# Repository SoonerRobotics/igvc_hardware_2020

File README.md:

# igvc_hardware_2020

PCBs for the IGVC competition.

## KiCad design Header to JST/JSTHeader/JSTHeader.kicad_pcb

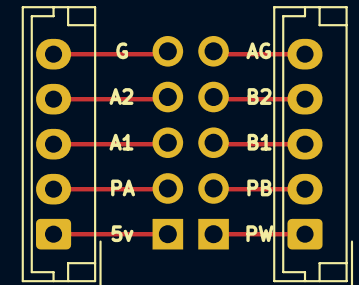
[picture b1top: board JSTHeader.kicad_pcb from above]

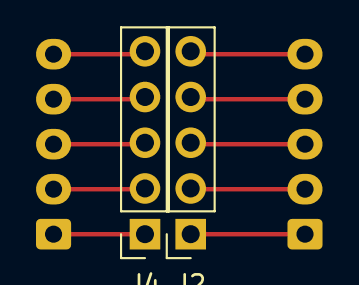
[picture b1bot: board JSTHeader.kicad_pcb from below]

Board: 2 copper layers, 4 parts (2 on the bottom side), 10 nets.

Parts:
J1, J3: Conn_01x05_Male; JST_EH_B5B-EH-A_1x05_P2.50mm_Vertical
J2, J4: Conn_01x05_Female; PinSocket_1x05_P2.54mm_Vertical

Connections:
unnamed: J1.1, J2.1
unnamed: J1.2, J2.2
unnamed: J1.3, J2.3
unnamed: J1.4, J2.4
unnamed: J1.5, J2.5
unnamed: J3.1, J4.1
unnamed: J3.2, J4.2
unnamed: J3.3, J4.3
unnamed: J3.4, J4.4
unnamed: J3.5, J4.5

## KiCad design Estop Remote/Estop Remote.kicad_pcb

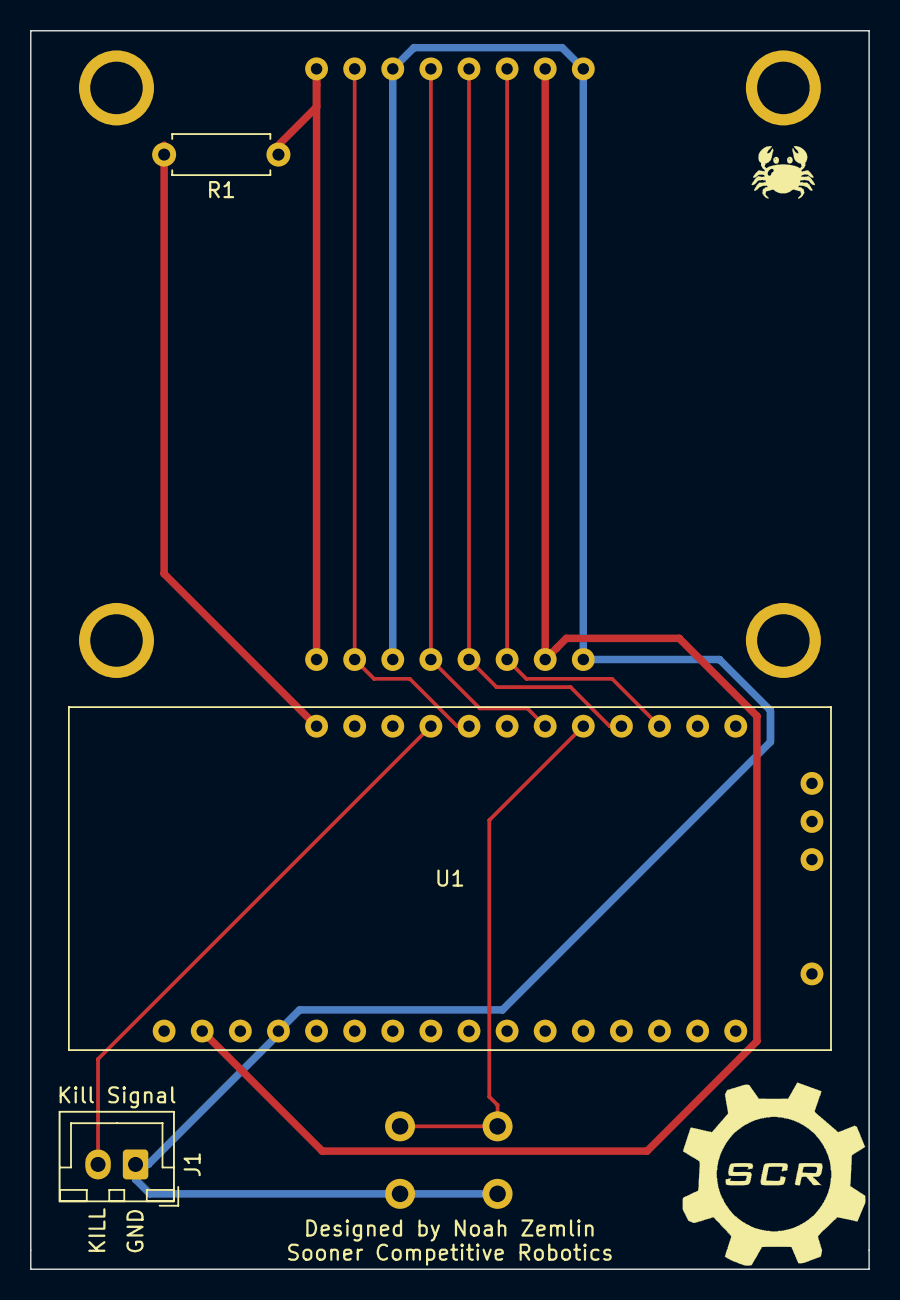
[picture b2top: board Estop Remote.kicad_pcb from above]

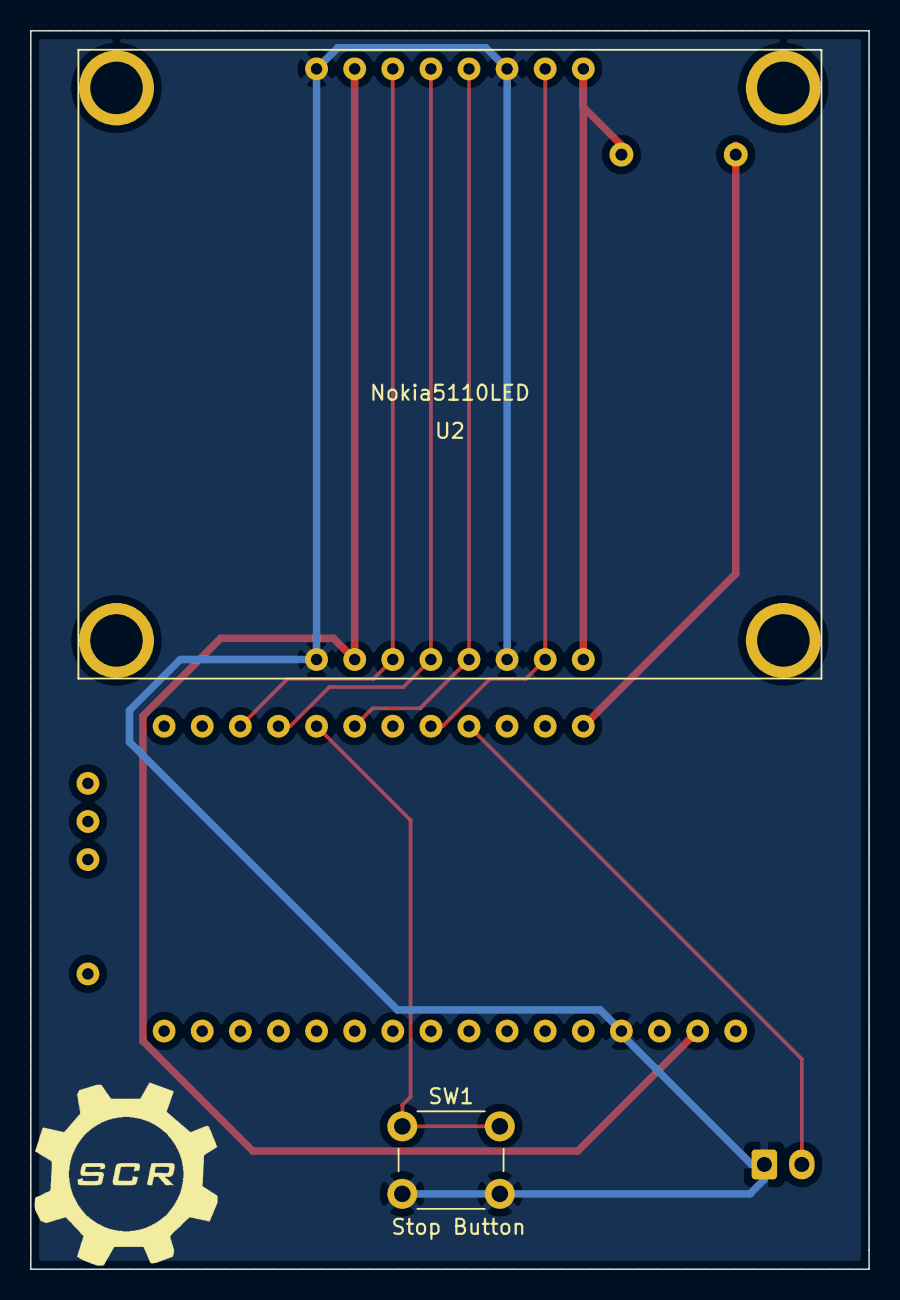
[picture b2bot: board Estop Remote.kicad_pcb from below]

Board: 2 copper layers, 55.9 x 82.6 mm, 5 parts (2 on the bottom side), 10 nets.

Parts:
J1: Kill Signal; JST_XH_B2B-XH-A_1x02_P2.50mm_Vertical
R1: 560; R_Axial_DIN0207_L6.3mm_D2.5mm_P7.62mm_Horizontal
SW1: Stop Button; SW_PUSH_6mm_H5mm
U1: AdafruitFeatherM0LoRa
U2: Nokia5110LED; AdafruitNokia5110

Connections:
+3V3: U1.31, U2.2
+5V: R1.2, U1.16
DSPL_DC: U1.10, U2.5
DSPL_DIN: U1.8, U2.4
DSPL_RST: U1.12, U2.7
DSPL_SCLK: U1.7, U2.3
GND: J1.1, SW1.2, U1.29, U2.1, U2.6
unnamed: R1.1, U2.8
SIG_KILL: J1.2, U1.13
SIG_STOP: SW1.1, U1.9

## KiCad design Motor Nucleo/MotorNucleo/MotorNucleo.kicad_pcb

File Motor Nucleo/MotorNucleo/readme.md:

# Nucleo motor controller board

The speed of the motor controller is controlled using PWM and the direction of the motor is controlled using the enable pins A and B. 

Each side of the robot has two motors connected together to provide more torque. The motors share a PWM signal and enable pins on their respective sides.

Vin is supplied using a buck converter that converts 12V to 5V

## Components
1x [Nucleo-L432](https://www.st.com/resource/en/datasheet/stm32l432kc.pdf)

4x 4 port JST connector

2x 3 port JST connector

1x 2 port JST connector
## Block diagram

###TODO

## Designers

- Tyler Julian - Designer - [TylerJulian](https://github.com/tylerjulian)

## Built With

- KiCAD - Used to create schematics and pcbs. 

## Errata
* revision 1 A level shifter was not needed due to the GP I/O pins being 5 volt tolerant. The schematic was also needlessly complicated and hard to read.

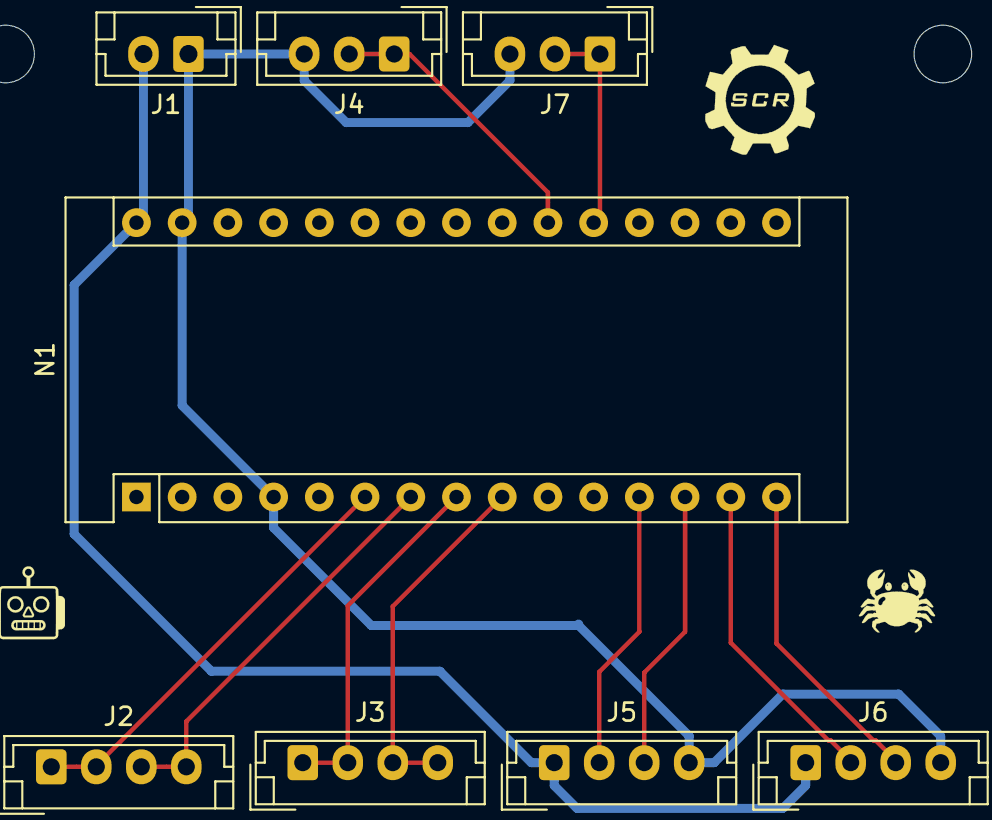
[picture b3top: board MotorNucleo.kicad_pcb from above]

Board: 2 copper layers, 8 parts (0 on the bottom side), 12 nets.

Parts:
J1: JST_01x02; JST_EH_B2B-EH-A_1x02_P2.50mm_Vertical
J2, J3, J5, J6: JST_01x04; JST_EH_B4B-EH-A_1x04_P2.50mm_Vertical
J4, J7: JST_01x03; JST_EH_B3B-EH-A_1x03_P2.50mm_Vertical
N1: Nucleo-L432KC; Arduino_Nano

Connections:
+5V: J1.2, J5.1, J6.1, N1.30
ENCODER_LEFT_A: J5.2, N1.12
ENCODER_LEFT_B: J5.3, N1.13
ENCODER_RIGHT_A: J6.2, N1.14
ENCODER_RIGHT_B: J6.3, N1.15
GND: J1.1, J4.3, J5.4, J6.4, J7.3, N1.4, N1.29
LEFT_EN_A: J2.1, J2.2, N1.6
LEFT_EN_B: J2.3, J2.4, N1.7
LEFT_PWM: J7.1, J7.2, N1.20
RIGHT_EN_A: J3.1, J3.2, N1.8
RIGHT_EN_B: J3.3, J3.4, N1.9
RIGHT_PWM: J4.1, J4.2, N1.21

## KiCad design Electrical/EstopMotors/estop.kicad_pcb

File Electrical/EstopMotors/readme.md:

# Motor controller estop overide

The direction of the motor is controlled with using two pins. Enable will override the inputs and output low when enable is low. 

The schematic has enough outputs for two motors.

## Components
4x [irf9530n mosfets](http://www.vishay.com/docs/91076/sihf9530.pdf)

8x 10k resistors

4x 1k resistors

2x 4 port JST connector

1x 3 port JST connector
## Block diagram

## Designers

- Tyler Julian - Designer - [TylerJulian](https://github.com/tylerjulian)

## Built With

- KiCAD - Used to create schematics and pcbs. 

## Errata
* revision 1's PCBs had the incorrect footprint for the jst connectors and the drain and source of the mosfets were switched.
* revision 2 had the wrong mosfet type. Intended mosfet is p-channel instead of n-channel. Updated schematic to reflect the switch to p-channel.

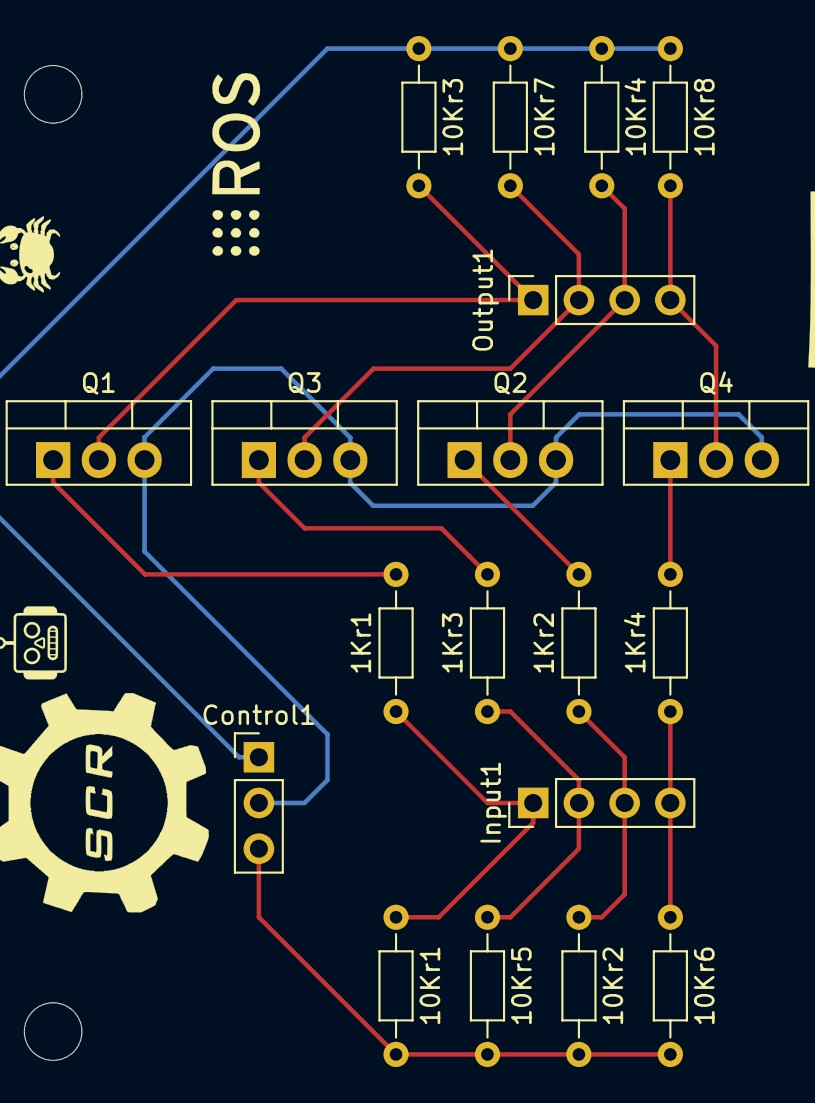
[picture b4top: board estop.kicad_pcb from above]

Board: 2 copper layers, 23 parts (0 on the bottom side), 15 nets.

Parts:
1Kr1, 1Kr2, 1Kr3, 1Kr4, 10Kr1, 10Kr2, 10Kr3, 10Kr4, 10Kr5, 10Kr6, 10Kr7, 10Kr8: ROX5SSJ1K8; R_Axial_DIN0204_L3.6mm_D1.6mm_P7.62mm_Horizontal
Control1: Conn_01x03; PinHeader_1x03_P2.54mm_Vertical
Input1: Conn_01x04; PinHeader_1x04_P2.54mm_Vertical
MountingHole1, MountingHole2, MountingHole3, MountingHole4: MOUNTINGHOLE; MountingHole_3.2mm_M3
Output1: Conn_01x04; PinSocket_1x04_P2.54mm_Vertical
Q1, Q2, Q3, Q4: IRF9530N; TO-220-3_Vertical

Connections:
Enable: Control1.2, Q1.3, Q2.3, Q3.3, Q4.3
GND: 10Kr3.1, 10Kr4.1, 10Kr7.1, 10Kr8.1, Control1.1
Input1: 1Kr1.1, 10Kr1.1, Input1.1
Input2: 1Kr3.1, 10Kr5.1, Input1.2
Input3: 1Kr2.1, 10Kr2.1, Input1.3
Input4: 1Kr4.1, 10Kr6.1, Input1.4
unnamed: 1Kr1.2, Q1.1
unnamed: 1Kr2.2, Q2.1
unnamed: 1Kr3.2, Q3.1
unnamed: 1Kr4.2, Q4.1
Output1: 10Kr3.2, Output1.1, Q1.2
Output2: 10Kr7.2, Output1.2, Q3.2
Output3: 10Kr4.2, Output1.3, Q2.2
Output4: 10Kr8.2, Output1.4, Q4.2
VCC: 10Kr1.2, 10Kr2.2, 10Kr5.2, 10Kr6.2, Control1.3

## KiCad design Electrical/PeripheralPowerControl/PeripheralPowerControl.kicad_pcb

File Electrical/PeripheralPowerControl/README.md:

# Peripheral Power Control Board

Enable and disable power to a peripheral component (such as a camera, raspberry pi, or arduino) and regulate voltage for the peripheral.

## Components
- [LM2956 Breakout Board](https://www.amazon.com/LM2596-Converter-3-0-40V-1-5-35V-Supply/dp/B01GJ0SC2C) - Buck Converter (can find on Amazon easily)
- [IPP120P04P4L03AKSA1](https://www.mouser.co.il/ProductDetail/Infineon-Technologies/IPP120P04P4L03AKSA1?qs=sGAEpiMZZMshyDBzk1%2FWi4lI00SCTc047yeVAvMQSdk%3D) - 120A rated Power PMOS
- [64600001003](https://www.mouser.co.il/ProductDetail/Littelfuse/64600001003?qs=J2dJc02fMkr9fpR3CPjt3Q==) - Fuse Holder

## Images
insert top view picture of PCB

## Designers

- Justin Kleiber - Designer - [jkleiber](https://github.com/jkleiber)

## Built With

- KiCAD - The PCB design software used

## Errata

TBD

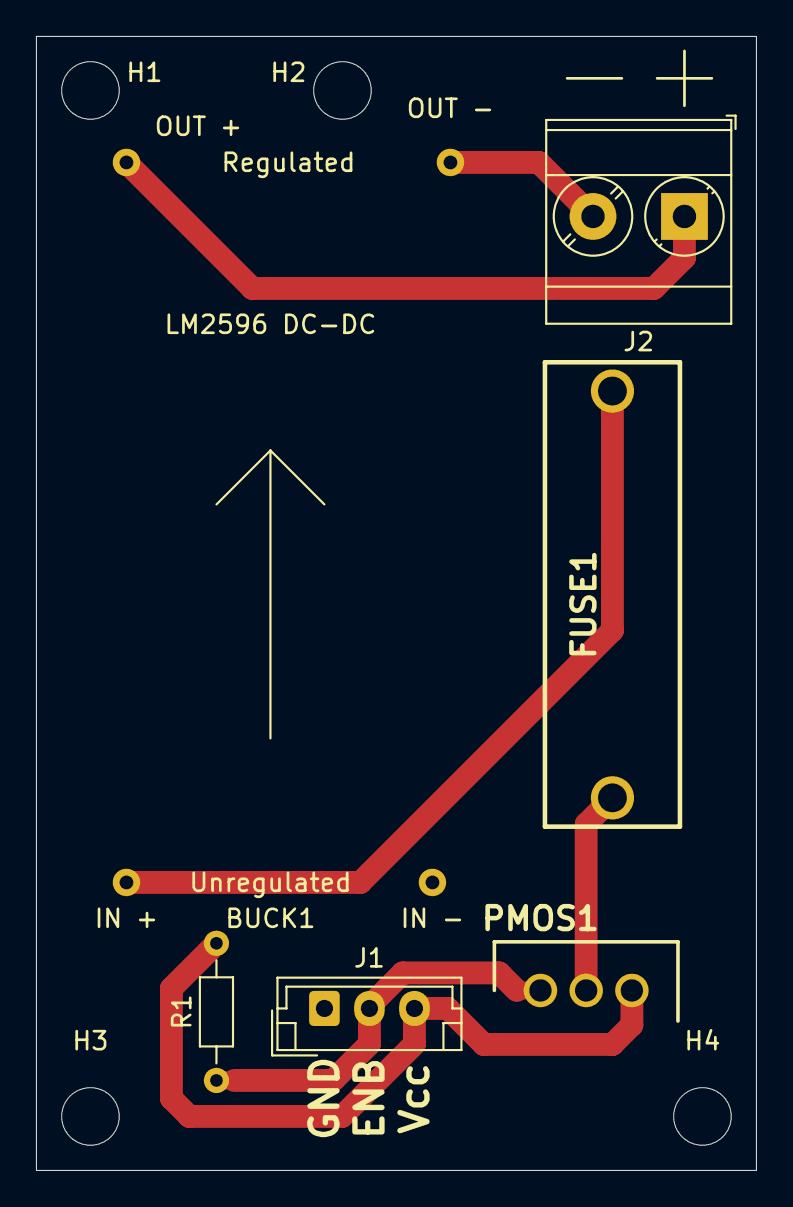
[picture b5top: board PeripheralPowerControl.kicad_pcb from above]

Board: 2 copper layers, 40.0 x 63.0 mm, 10 parts (0 on the bottom side), 7 nets.

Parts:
BUCK1: LM2596
FUSE1: 64600001003; 646-SERIESHOLDER
H1, H2, H3, H4: MountingHole; MountingHole_3.2mm_M3
J1: Conn_01x03; JST_EH_B3B-EH-A_1x03_P2.50mm_Vertical
J2: Screw_Terminal_01x02; TerminalBlock_Phoenix_MKDS-3-2-5.08_1x02_P5.08mm_Horizontal
PMOS1: IPP120P04P4L03AKSA1; TO254P440X1000X2110-3P
R1: R; R_Axial_DIN0204_L3.6mm_D1.6mm_P7.62mm_Horizontal

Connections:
GND: BUCK1.1, J1.1
unnamed: BUCK1.2, FUSE1.2
unnamed: BUCK1.3, J2.2
unnamed: BUCK1.4, J2.1
unnamed: FUSE1.1, PMOS1.2
unnamed: J1.2, PMOS1.1, R1.1
unnamed: J1.3, PMOS1.3, R1.2

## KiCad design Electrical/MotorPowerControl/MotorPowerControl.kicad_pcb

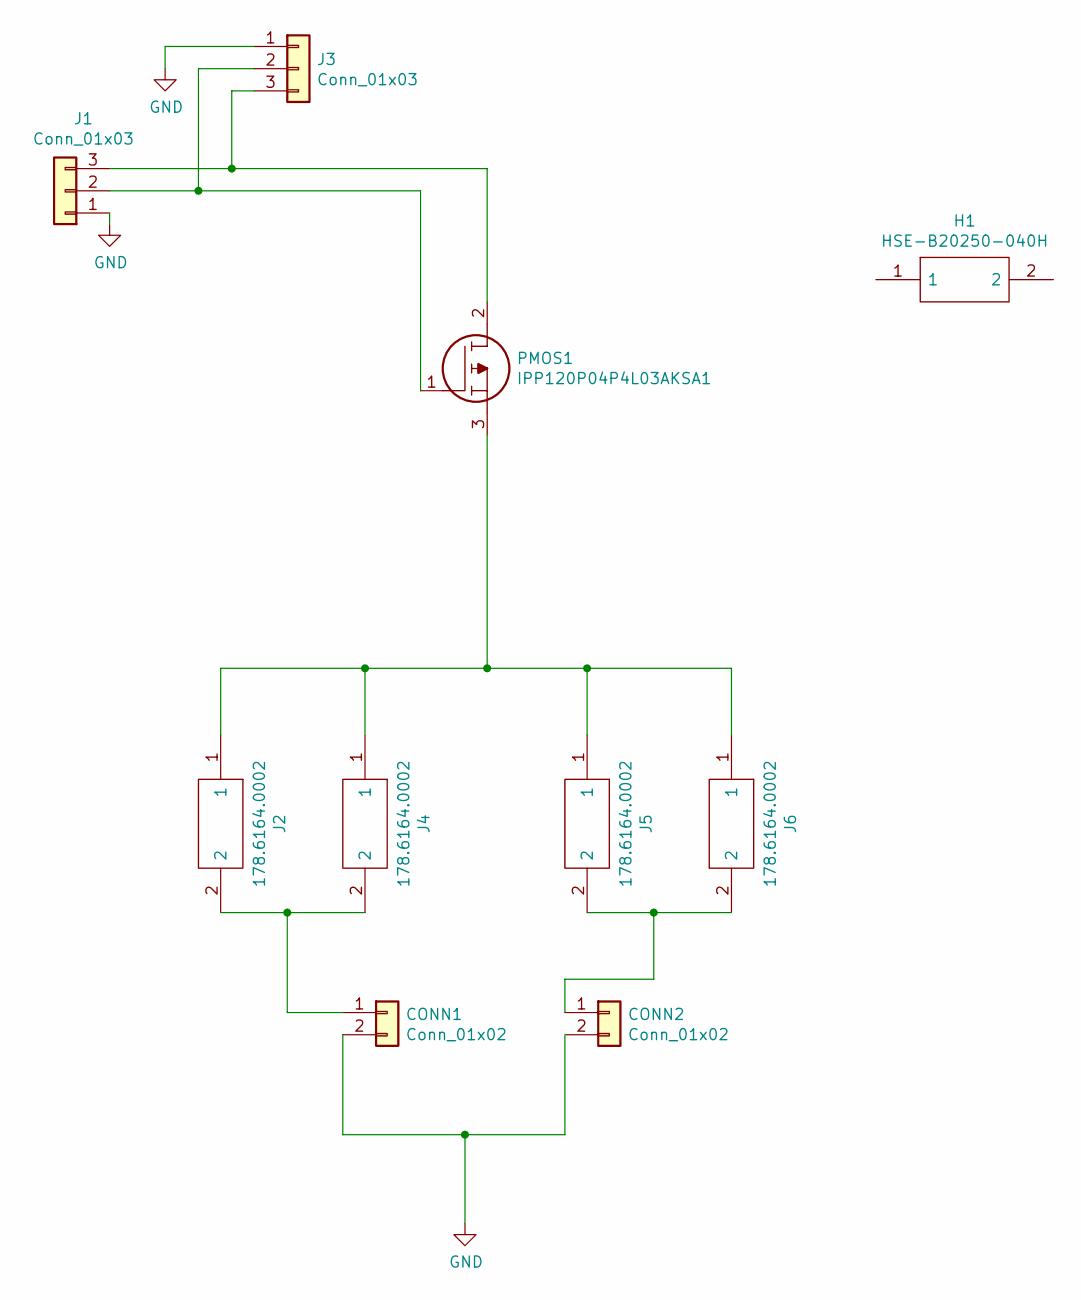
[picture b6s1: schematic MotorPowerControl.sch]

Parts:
CONN1, CONN2: Conn_01x02; SolderWirePad_1x02_P7.62mm_Drill2.5mm
H1: HSE-B20250-040H; HSEB20250040H; Mouser Part Number 490-HSE-B20250-040H
J1, J3: Conn_01x03; SolderWirePad_1x03_P7.62mm_Drill2.5mm
J2, J4, J5, J6: 178.6164.0002; 178.6164.0002_1; Mouser Part Number 576-178.6164.0002
PMOS1: IPP120P04P4L03AKSA1; TO254P440X1000X2110-3P; Mouser Part Number 726-IPP120P04P4L03AK

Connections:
GND: CONN1.2, CONN2.2, J1.1, J3.1
unnamed: CONN1.1, J2.2, J4.2
unnamed: CONN2.1, J5.2, J6.2
unnamed: J1.2, J3.2, PMOS1.1
unnamed: J1.3, J3.3, PMOS1.2
unnamed: J2.1, J4.1, J5.1, J6.1, PMOS1.3

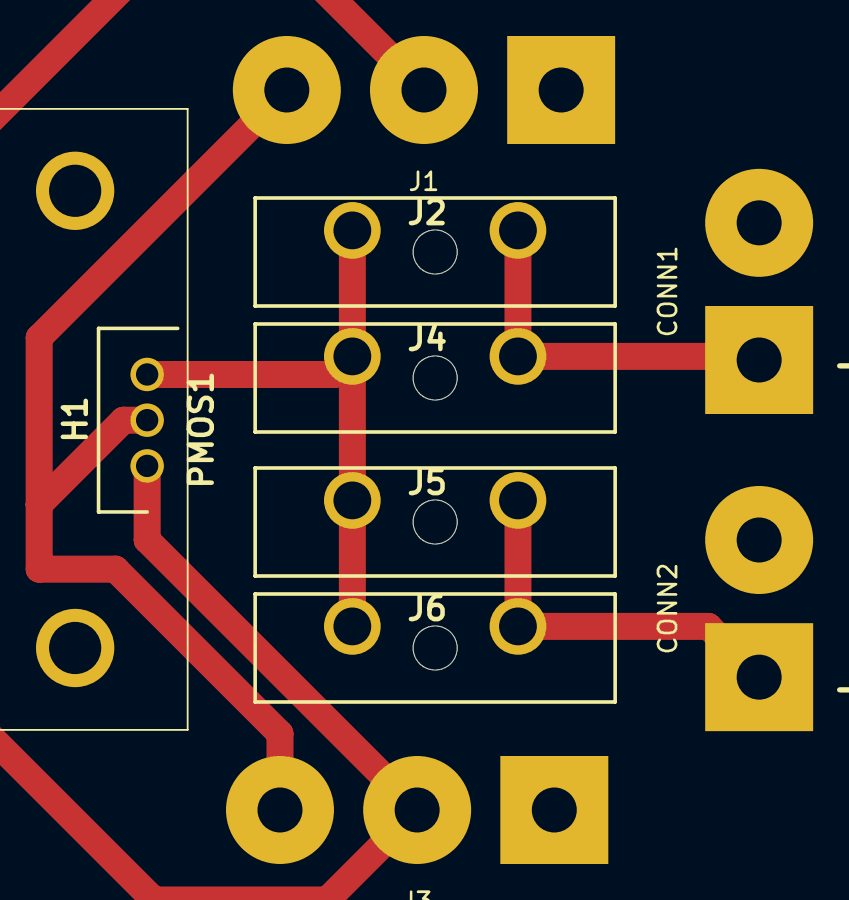
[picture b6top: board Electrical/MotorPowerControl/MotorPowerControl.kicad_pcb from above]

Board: 2 copper layers, 10 parts (0 on the bottom side), 6 nets.

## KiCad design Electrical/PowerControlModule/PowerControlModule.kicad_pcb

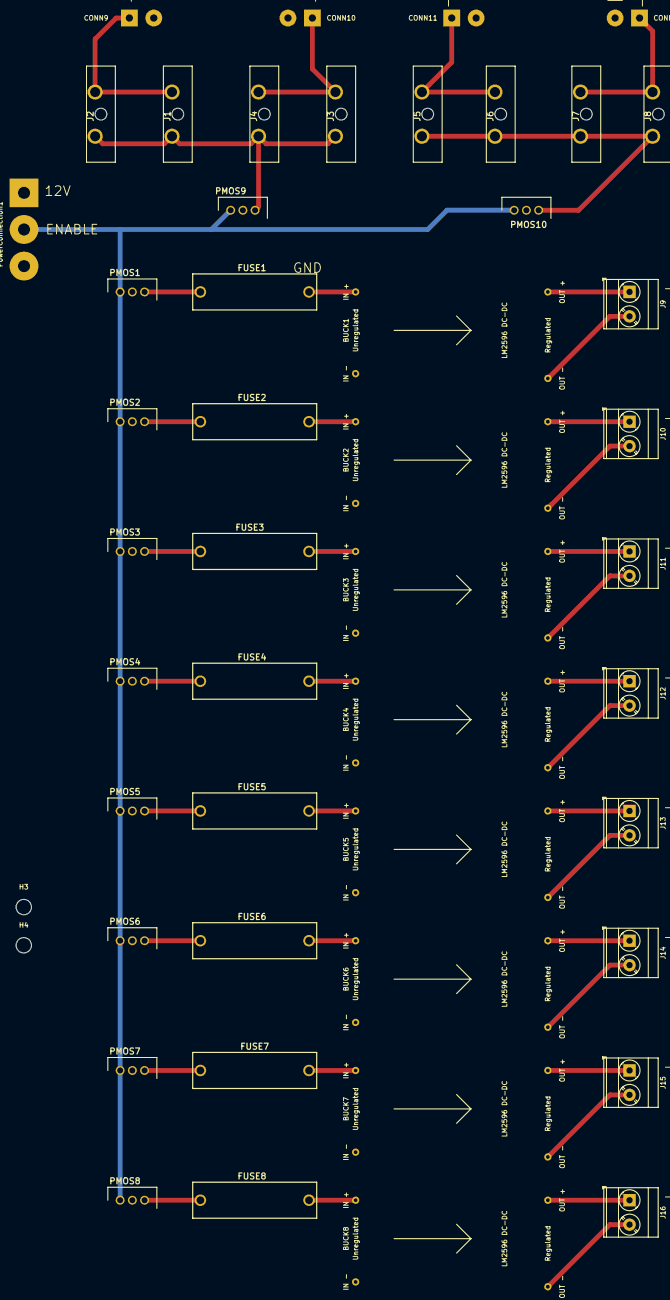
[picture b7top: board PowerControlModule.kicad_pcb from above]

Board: 4 copper layers, 51 parts (0 on the bottom side), 41 nets.

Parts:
BUCK1, BUCK2, BUCK3, BUCK4, BUCK5, BUCK6, BUCK7, BUCK8: LM2596
CONN9, CONN10, CONN11, CONN12: Conn_01x02; SolderWirePad_1x02_P5.08mm_Drill1.5mm
FUSE1, FUSE2, FUSE3, FUSE4, FUSE5, FUSE6, FUSE7, FUSE8: 64600001003; 646-SERIESHOLDER
H1, H2, H3, H4: MountingHole; MountingHole_3.2mm_M3
J1, J2, J3, J4, J5, J6, J7, J8: 178.6164.0002; 178.6164.0002_1
J9, J10, J11, J12, J13, J14, J15, J16: Screw_Terminal_01x02; TerminalBlock_Phoenix_MKDS-3-2-5.08_1x02_P5.08mm_Horizontal
PMOS1, PMOS2, PMOS3, PMOS4, PMOS5, PMOS6, PMOS7, PMOS8, PMOS9, PMOS10: IPP120P04P4L03AKSA1; TO254P440X1000X2110-3P
PowerConnection1: Conn_01x03; SolderWirePad_1x03_P7.62mm_Drill2.5mm

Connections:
+12V: PMOS1.2, PMOS2.2, PMOS3.2, PMOS4.2, PMOS5.2, PMOS6.2, PMOS7.2, PMOS8.2, PMOS9.2, PMOS10.2, PowerConnection1.1
/ENABLE: PMOS1.1, PMOS2.1, PMOS3.1, PMOS4.1, PMOS5.1, PMOS6.1, PMOS7.1, PMOS8.1, PMOS9.1, PMOS10.1, PowerConnection1.2
GND: BUCK1.1, BUCK2.1, BUCK3.1, BUCK4.1, BUCK5.1, BUCK6.1, BUCK7.1, BUCK8.1, CONN9.2, CONN10.2, CONN11.2, CONN12.2, PowerConnection1.3
unnamed: BUCK1.2, FUSE1.2
unnamed: BUCK1.3, J9.2
unnamed: BUCK1.4, J9.1
unnamed: BUCK2.2, FUSE2.2
unnamed: BUCK2.3, J10.2
unnamed: BUCK2.4, J10.1
unnamed: BUCK3.2, FUSE3.2
unnamed: BUCK3.3, J11.2
unnamed: BUCK3.4, J11.1
unnamed: BUCK4.2, FUSE4.2
unnamed: BUCK4.3, J12.2
unnamed: BUCK4.4, J12.1
unnamed: BUCK5.2, FUSE5.2
unnamed: BUCK5.3, J13.2
unnamed: BUCK5.4, J13.1
unnamed: BUCK6.2, FUSE6.2
unnamed: BUCK6.3, J14.2
unnamed: BUCK6.4, J14.1
unnamed: BUCK7.2, FUSE7.2
unnamed: BUCK7.3, J15.2
unnamed: BUCK7.4, J15.1
unnamed: BUCK8.2, FUSE8.2
unnamed: BUCK8.3, J16.2
unnamed: BUCK8.4, J16.1
unnamed: CONN9.1, J1.2, J2.2
unnamed: CONN10.1, J3.2, J4.2
unnamed: CONN11.1, J5.2, J6.2
unnamed: CONN12.1, J7.2, J8.2
unnamed: FUSE1.1, PMOS1.3
unnamed: FUSE2.1, PMOS2.3
unnamed: FUSE3.1, PMOS3.3
unnamed: FUSE4.1, PMOS4.3
unnamed: FUSE5.1, PMOS5.3
unnamed: FUSE6.1, PMOS6.3
unnamed: FUSE7.1, PMOS7.3
unnamed: FUSE8.1, PMOS8.3
unnamed: J1.1, J2.1, J3.1, J4.1, PMOS9.3
unnamed: J5.1, J6.1, J7.1, J8.1, PMOS10.3

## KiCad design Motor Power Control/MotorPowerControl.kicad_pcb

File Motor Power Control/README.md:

# Motor Power Control Board

Enable and disable power to a peripheral component (such as a camera, Raspberry Pi, or Arduino) and regulate voltage for the peripheral.

## Components

- [LM2956 Breakout Board](https://www.amazon.com/LM2596-Converter-3-0-40V-1-5-35V-Supply/dp/B01GJ0SC2C) - Buck Converter (can find on Amazon easily)
- [IPP120P04P4L03AKSA1](https://www.mouser.co.il/ProductDetail/Infineon-Technologies/IPP120P04P4L03AKSA1?qs=sGAEpiMZZMshyDBzk1%2FWi4lI00SCTc047yeVAvMQSdk%3D) - 120A rated Power PMOS
- [64600001003](https://www.mouser.co.il/ProductDetail/Littelfuse/64600001003?qs=J2dJc02fMkr9fpR3CPjt3Q==) - Fuse Holder

## Images

- insert top view picture of PCB

## Designers

- XXX - YYY - [ZZZ](https://github.com/jkleiber)

## Built With

- KiCAD - The PCB design software used

## Errata

- TBD

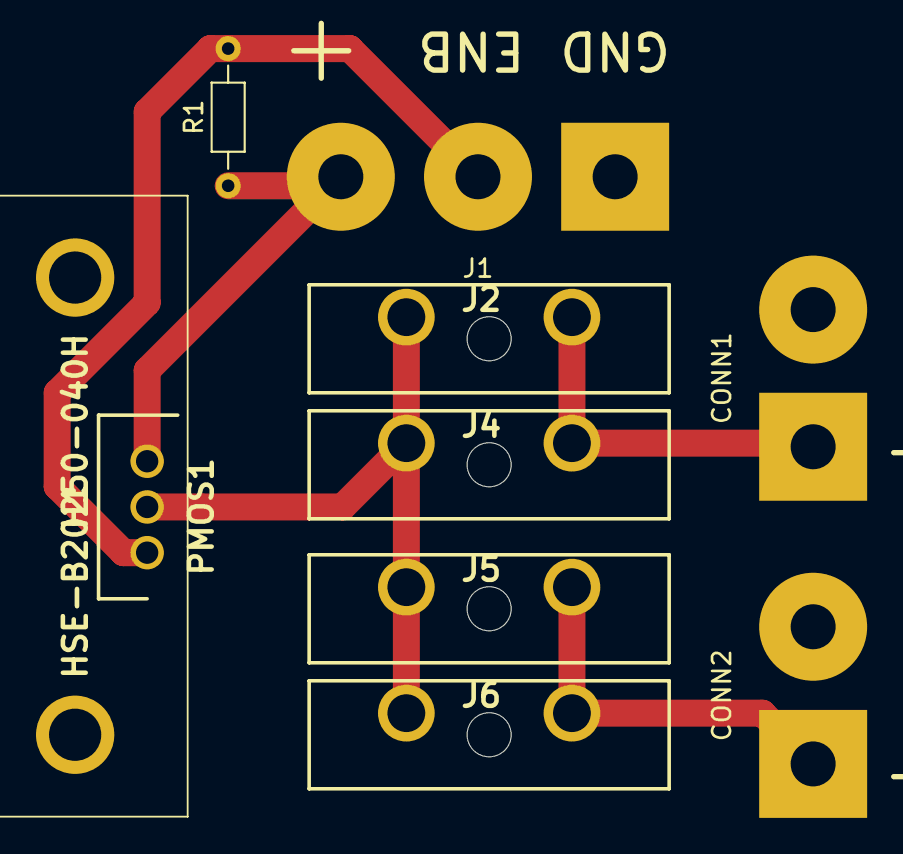
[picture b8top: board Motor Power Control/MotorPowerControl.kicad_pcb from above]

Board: 2 copper layers, 14 parts (0 on the bottom side), 6 nets.

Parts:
CONN1, CONN2: Conn_01x02; SolderWirePad_1x02_P7.62mm_Drill2.5mm
H1: HSE-B20250-040H; HSEB20250040H
H2, H3, H4, H5: MountingHole; MountingHole_3.2mm_M3
J1: Conn_01x03; SolderWirePad_1x03_P7.62mm_Drill2.5mm
J2, J4, J5, J6: 178.6164.0002; 178.6164.0002_1
PMOS1: IPP120P04P4L03AKSA1; TO254P440X1000X2110-3P
R1: R; R_Axial_DIN0204_L3.6mm_D1.6mm_P7.62mm_Horizontal

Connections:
GND: CONN1.2, CONN2.2, J1.1
unnamed: CONN1.1, J2.2, J4.2
unnamed: CONN2.1, J5.2, J6.2
unnamed: J1.2, PMOS1.1, R1.2
unnamed: J1.3, PMOS1.3, R1.1
unnamed: J2.1, J4.1, J5.1, J6.1, PMOS1.2

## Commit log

2019-08-02 Initial schematic for the transmitter/receiver estop. Does not include power sources in schematic.
2019-09-12 Begins work on the power control module
2019-09-12 Testing import of power mosfet
2019-09-20 posted picture of motor control circuit
2019-09-20 Lays out peripherals and motor control power distribution
    Paginates the schematic for ease of editing
2019-09-24 Adds new part library for SCR stuff. Gets buck converters and connectors to show up on PCB layout
2019-09-24 Lays out power distribution board on PCB. Need to make 4 layer setup before routing. Also need to change motor output footprint
2019-09-25 Routes PCM as a 4 layer board
2019-09-25 Fixes silkscreen stuff and adds ground connection for motor control battery connection
2019-09-25 Power control module grounding and power plane fixes
2019-09-26 Rearranges mosfets, fuses and buck converters in correct order. Need to add heatsinks to design and confirm hole sizes. Also need to add safety module eventually
2019-09-26 Peripheral changes and rewired PCB
2019-10-02 Splits project into multiple modules, peripherals, motors, and safety
2019-10-02 Adds ground plane to the peripheral board
2019-10-03 Updates BOM for motor power control
2019-10-08 Verified Peripheral and Motor power controllers
2019-10-22 Adafruit M0 LoRa Control
2019-11-26 Upload motor estop schematic and pcb
2020-01-29 Adds notes for the peripheral power controller
2020-01-30 Beefs up traces of peripheral power module to 50 mils - aiming for 10 degC temp rise
2020-01-30 Add readme for peripheral power control module
2020-01-30 Updates readme to add links
2020-02-04 Updated the motor estop
2020-02-04 Further update to estop schematic. Schematic is not updated.
2020-02-07 Updated Schematic. The load/output were not connected to drain.
2020-02-12 Updated errata and components
2020-02-12 uploaded Diagram
2020-02-13 updated to rev 2
2020-02-13 updated pcb and schematic to rev3
2020-02-13 updated Block Diagram
2020-02-17 updated to rev 3 and added correct designators. Uploaded rev 3 schematic
2020-02-21 Adds PDFs to show schematics and comments the motor power module some
2020-02-21 Clean up repo
2020-02-21 Add gitignore file
2020-02-21 Update gitignore
2020-02-21 Uploaded Revision 1 of Motor Nucleo schematic
2020-02-25 Create Safety Receiver Schematic
2020-02-25 Updated schematic to revision 2.
2020-02-26 updated schematic to include labels instead of wires
2020-02-27 updated designators
2020-02-27 Uploaded PCB for Motor Nucleo breakout board
2020-02-27 Upload PCB pdf
2020-03-03 Estop Remote First Draft
2020-03-04 Attached LED pin and fix power delivery
2020-03-04 Added ground plane and Antenna net name
2020-03-04 Fixed mounting holes and resistor position
2020-03-06 Fixed Silkscreen
2020-03-08 Centered Estop Remote schematic
